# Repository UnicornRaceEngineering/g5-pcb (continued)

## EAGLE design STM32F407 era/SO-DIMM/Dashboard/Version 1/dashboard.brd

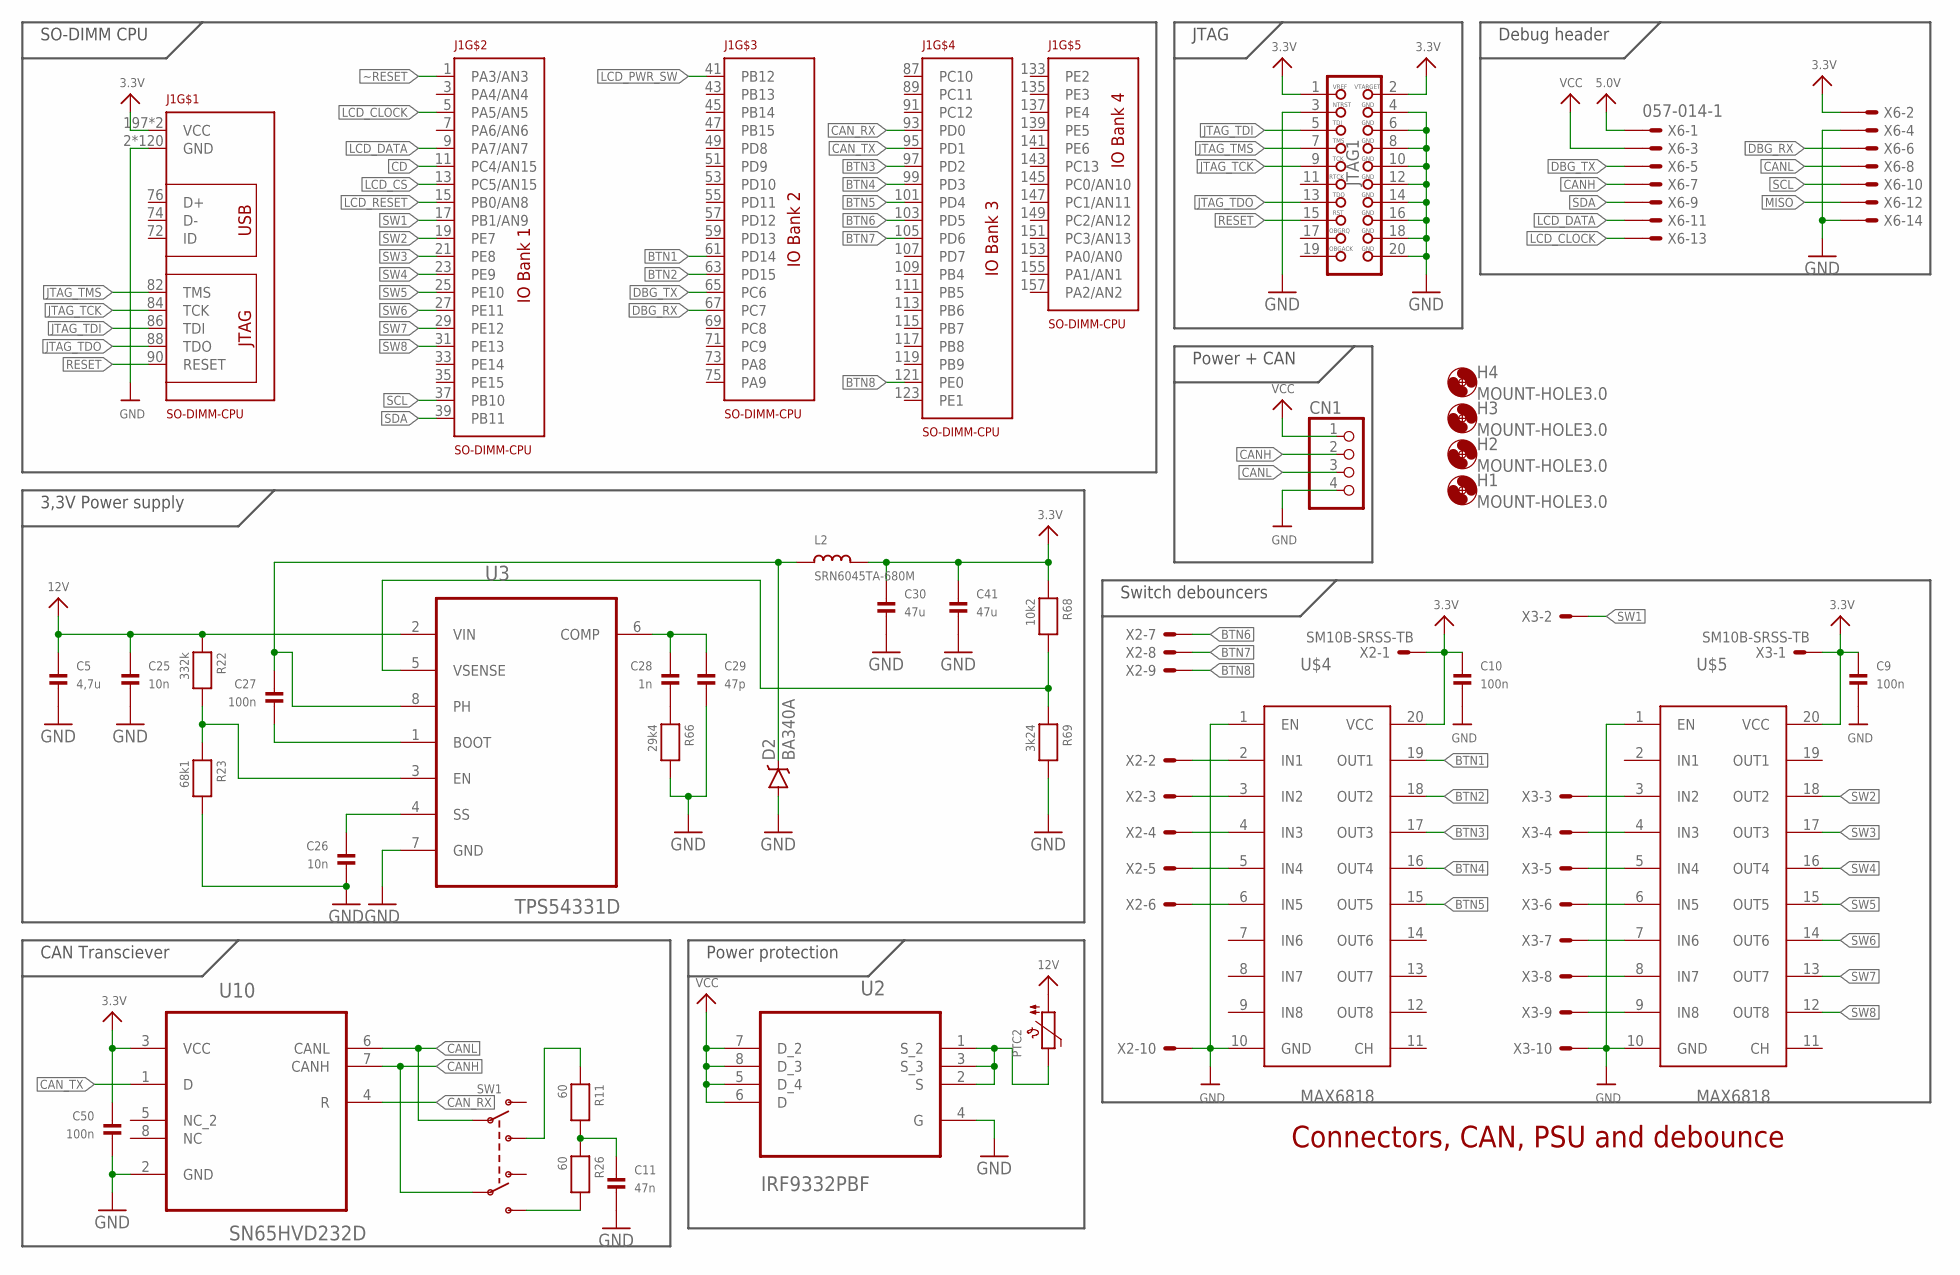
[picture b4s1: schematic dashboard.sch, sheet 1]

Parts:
C5: 4,7u; _0805
C9, C10, C27, C50: 100n; _0603
C11: 47n; _0603
C25, C26: 10n; _0603
C28: 1n; _0603
C29: 47p; _0603
C30, C41: 47u; _0805
CN1: JST_4PIN; JSTPH4
D2: BA340A; SMA-DIODE
H1, H2, H3, H4: MOUNT-HOLE3.0; 3,0
J1: SO-DIMM-CPU; SODIMM-CONNECTOR-2.5V
JTAG1: JTAG-ARM
L2: SRN6045TA-680M; INDUCTOR_6X6MM_TDK_VLC6045
PTC2: PTC1812
R11, R26: 60; _0603
R22: 332k; _0603
R23: 68k1; _0603
R66: 29k4; _0603
R68: 10k2; _0603
R69: 3k24; _0603
SW1: SWITCH_DPDT; DPDT_SMT_JS202011SCQN
U2: IRF9332PBF; SOIC127P600X175-8N
U3: TPS54331D; SOIC127P600X175-8N
U10: SN65HVD232D; SOIC127P600X175-8N
U$4, U$5: MAX6818; SOP20
X2, X3: SM10B-SRSS-TB
X6: 057-014-1

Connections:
3.3V: C9.1, C10.1, C30.1, C41.1, C50.1, J1.197 (VCC), J1.199 (VCC), JTAG1.1, JTAG1.2, L2.P$2 (2), R68.1, U10.3 (VCC), U$4.20 (VCC), U$5.20 (VCC), X2.1, X3.1, X6.2; also elsewhere on the board
5.0V: X6.1
12V: C5.1, C25.1, PTC2.P$1 (1), R22.1, U3.2 (VIN)
BTN1: J1.61 (PD14), U$4.19 (OUT1)
BTN2: J1.63 (PD15), U$4.18 (OUT2)
BTN3: J1.97 (PD2), U$4.17 (OUT3)
BTN4: J1.99 (PD3), U$4.16 (OUT4)
BTN5: J1.101 (PD4), U$4.15 (OUT5)
BTN6: J1.103 (PD5), X2.7
BTN7: J1.105 (PD6), X2.8
BTN8: J1.121 (PE0), X2.9
CANH: CN1.2, SW1.P$5 (P2), U10.7 (CANH), X6.7
CANL: CN1.3, SW1.P$2 (P1), U10.6 (CANL), X6.8
CAN_RX: J1.93 (PD0), U10.4 (R)
CAN_TX: J1.95 (PD1), U10.1 (D)
CD: J1.11 (PC4/AN15); also elsewhere on the board
DBG_RX: J1.67 (PC7), X6.6
DBG_TX: J1.65 (PC6), X6.5
GND: C5.2, C9.2, C10.2, C11.2, C25.2, C26.2, C29.2, C30.2, C41.2, C50.2, CN1.4, D2.A, J1.2 (GND), J1.4 (GND), J1.6 (GND), J1.8 (GND), J1.10 (GND), J1.12 (GND), J1.14 (GND), J1.16 (GND), J1.18 (GND), J1.20 (GND), J1.22 (GND), J1.24 (GND), J1.26 (GND), J1.28 (GND), J1.30 (GND), J1.32 (GND), J1.34 (GND), J1.36 (GND), J1.38 (GND), J1.40 (GND), J1.42 (GND), J1.44 (GND), J1.46 (GND), J1.48 (GND), J1.50 (GND), J1.52 (GND), J1.54 (GND), J1.56 (GND), J1.58 (GND), J1.60 (GND), J1.62 (GND), J1.64 (GND), J1.66 (GND), J1.68 (GND), J1.70 (GND), J1.77 (GND), J1.78 (GND), J1.79 (GND), J1.80 (GND), J1.81 (GND), J1.83 (GND), J1.85 (GND), J1.92 (GND), J1.94 (GND), J1.96 (GND), J1.98 (GND), J1.100 (GND), J1.102 (GND), J1.104 (GND), J1.106 (GND), J1.108 (GND), J1.110 (GND), J1.112 (GND), J1.114 (GND), J1.116 (GND), J1.118 (GND), J1.120 (GND), J1.122 (GND), J1.124 (GND), J1.125 (GND), J1.126 (GND), J1.127 (GND), J1.128 (GND), J1.129 (GND), J1.130 (GND), J1.131 (GND), J1.132 (GND), J1.134 (GND), J1.136 (GND), J1.138 (GND), J1.140 (GND), J1.142 (GND), J1.144 (GND), J1.146 (GND), J1.148 (GND), J1.150 (GND), J1.152 (GND), J1.154 (GND), J1.156 (GND), J1.158 (GND), J1.159 (GND), J1.160 (GND), J1.161 (GND), J1.162 (GND), J1.163 (GND), J1.164 (GND), J1.165 (GND), J1.166 (GND), J1.167 (GND), J1.168 (GND), J1.169 (GND), J1.170 (GND), J1.171 (GND), J1.172 (GND), J1.173 (GND), J1.174 (GND), J1.175 (GND), J1.176 (GND), J1.177 (GND), J1.178 (GND), J1.179 (GND), J1.180 (GND), J1.181 (GND), J1.182 (GND), J1.183 (GND), J1.184 (GND), J1.185 (GND), J1.186 (GND), J1.187 (GND), J1.188 (GND), J1.189 (GND), J1.190 (GND), J1.191 (GND), J1.192 (GND), J1.193 (GND), J1.194 (GND), J1.195 (GND), J1.196 (GND), J1.198 (GND), J1.200 (GND), JTAG1.3, JTAG1.4, JTAG1.6, JTAG1.8, JTAG1.10, JTAG1.12, JTAG1.14, JTAG1.16, JTAG1.18, JTAG1.20, R23.2, R66.2, R69.2, U2.4 (G), U3.7 (GND), U10.2 (GND), U$4.1 (EN), U$4.10 (GND), U$5.1 (EN), U$5.10 (GND), X2.10, X3.10, X6.4, X6.14; also elsewhere on the board
JTAG_TCK: J1.84 (TCK), JTAG1.9
JTAG_TDI: J1.86 (TDI), JTAG1.5
JTAG_TDO: J1.88 (TDO), JTAG1.13
JTAG_TMS: J1.82 (TMS), JTAG1.7
LCD_CLOCK: J1.5 (PA5/AN5), X6.13; also elsewhere on the board
LCD_CS: J1.13 (PC5/AN15); also elsewhere on the board
LCD_DATA: J1.9 (PA7/AN7), X6.11; also elsewhere on the board
LCD_PWR_SW: J1.41 (PB12); also elsewhere on the board
LCD_RESET: J1.15 (PB0/AN8); also elsewhere on the board
MISO: X6.12
unnamed: C26.1, U3.4 (SS)
unnamed: R22.2, R23.1, U3.3 (EN)
unnamed: C27.2, U3.1 (BOOT)
unnamed: C27.1, D2.C, L2.P$1 (1), U3.8 (PH)
unnamed: C28.2, R66.1
unnamed: C28.1, C29.1, U3.6 (COMP)
unnamed: R68.2, R69.1, U3.5 (VSENSE)
unnamed: PTC2.P$2 (2), U2.1 (S_2), U2.2 (S), U2.3 (S_3)
unnamed: R26.2, SW1.P$4 (S2)
unnamed: C11.1, R11.2, R26.1
unnamed: U$4.2 (IN1), X2.2
unnamed: U$5.3 (IN2), X3.3
unnamed: U$5.4 (IN3), X3.4
unnamed: U$5.5 (IN4), X3.5
unnamed: U$5.6 (IN5), X3.6
unnamed: U$5.7 (IN6), X3.7
unnamed: U$5.8 (IN7), X3.8
unnamed: U$5.9 (IN8), X3.9
unnamed: U$4.3 (IN2), X2.3
unnamed: U$4.4 (IN3), X2.4
unnamed: U$4.5 (IN4), X2.5
unnamed: U$4.6 (IN5), X2.6
unnamed: R11.1, SW1.P$3 (S1)
RESET: J1.90 (RESET), JTAG1.15
SCL: J1.37 (PB10), X6.10; also elsewhere on the board
SDA: J1.39 (PB11), X6.9; also elsewhere on the board
SW1: J1.17 (PB1/AN9), X3.2
SW2: J1.19 (PE7), U$5.18 (OUT2)
SW3: J1.21 (PE8), U$5.17 (OUT3)
SW4: J1.23 (PE9), U$5.16 (OUT4)
SW5: J1.25 (PE10), U$5.15 (OUT5)
SW6: J1.27 (PE11), U$5.14 (OUT6)
SW7: J1.29 (PE12), U$5.13 (OUT7)
SW8: J1.31 (PE13), U$5.12 (OUT8)
VCC: CN1.1, U2.5 (D_4), U2.6 (D), U2.7 (D_2), U2.8 (D_3), X6.3
~RESET: J1.1 (PA3/AN3); also elsewhere on the board

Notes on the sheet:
3,3V Power supply
Power protection
CAN Transciever
JTAG
Debug header
SO-DIMM CPU
Power + CAN
Switch debouncers
Connectors, CAN, PSU and debounce

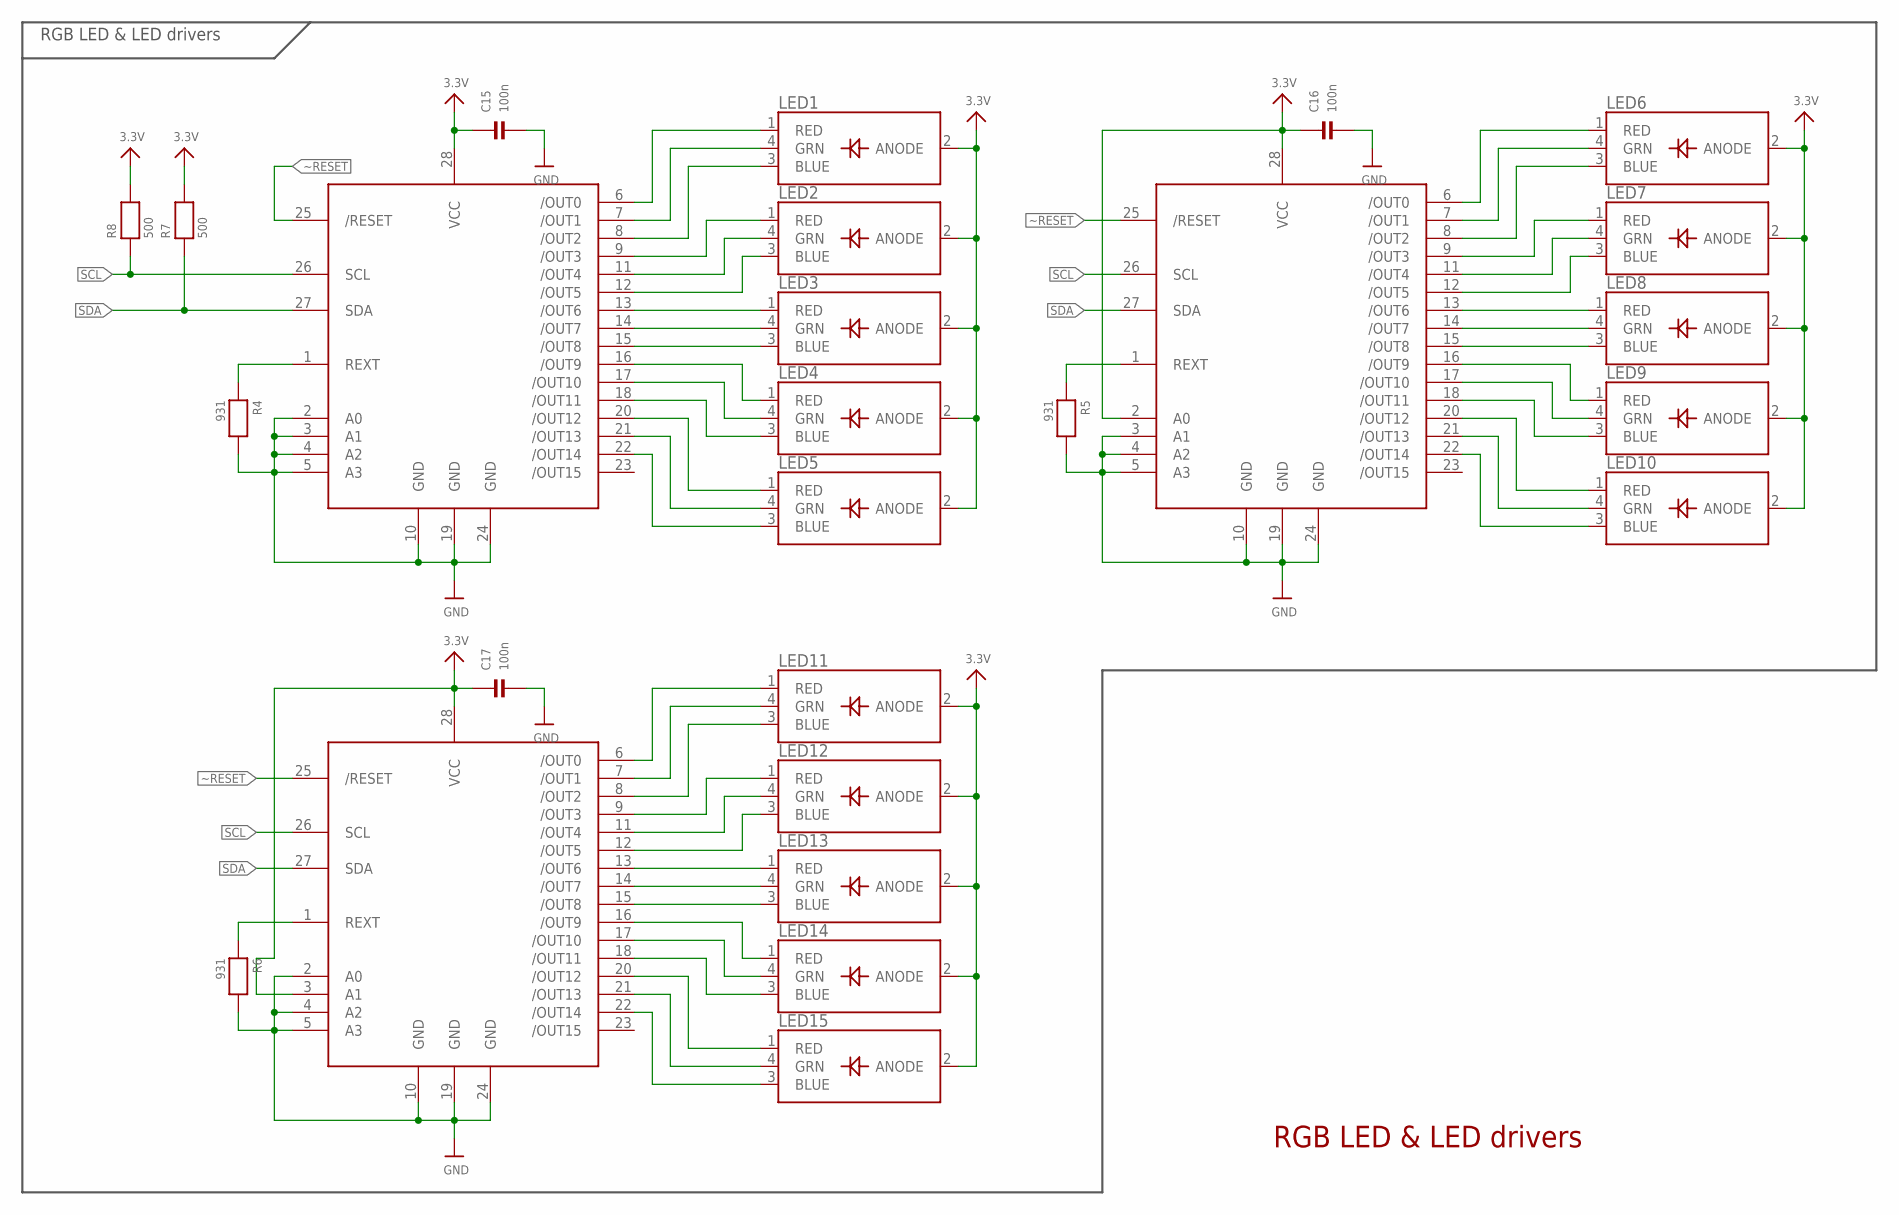
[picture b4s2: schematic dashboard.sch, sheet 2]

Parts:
C15, C16, C17: 100n; _0603
LED1, LED2, LED3, LED4, LED5, LED6, LED7, LED8, LED9, LED10, LED11, LED12, LED13, LED14, LED15: LED_RGB_PLCC4; RGBLED_PLCC4
R4, R5, R6: 931; _0603
R7, R8: 500; _0603
U$30, U$33, U$36: TLC59116; TSSOP28

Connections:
3.3V: C15.1, C16.1, C17.1, LED1.2 (ANODE), LED2.2 (ANODE), LED3.2 (ANODE), LED4.2 (ANODE), LED5.2 (ANODE), LED6.2 (ANODE), LED7.2 (ANODE), LED8.2 (ANODE), LED9.2 (ANODE), LED10.2 (ANODE), LED11.2 (ANODE), LED12.2 (ANODE), LED13.2 (ANODE), LED14.2 (ANODE), LED15.2 (ANODE), R7.2, R8.2, U$30.28 (VCC), U$33.2 (A0), U$33.28 (VCC), U$36.3 (A1), U$36.28 (VCC); also elsewhere on the board
GND: C15.2, C16.2, C17.2, R4.2, R5.2, R6.2, U$30.2 (A0), U$30.3 (A1), U$30.4 (A2), U$30.5 (A3), U$30.10 (GND), U$30.19 (GND), U$30.24 (GND), U$33.3 (A1), U$33.4 (A2), U$33.5 (A3), U$33.10 (GND), U$33.19 (GND), U$33.24 (GND), U$36.2 (A0), U$36.4 (A2), U$36.5 (A3), U$36.10 (GND), U$36.19 (GND), U$36.24 (GND); also elsewhere on the board
unnamed: LED1.1 (RED), U$30.6 (/OUT0)
unnamed: LED1.4 (GRN), U$30.7 (/OUT1)
unnamed: LED1.3 (BLUE), U$30.8 (/OUT2)
unnamed: LED2.1 (RED), U$30.9 (/OUT3)
unnamed: LED2.4 (GRN), U$30.11 (/OUT4)
unnamed: LED2.3 (BLUE), U$30.12 (/OUT5)
unnamed: LED3.1 (RED), U$30.13 (/OUT6)
unnamed: LED3.4 (GRN), U$30.14 (/OUT7)
unnamed: LED3.3 (BLUE), U$30.15 (/OUT8)
unnamed: LED4.1 (RED), U$30.16 (/OUT9)
unnamed: LED4.4 (GRN), U$30.17 (/OUT10)
unnamed: LED4.3 (BLUE), U$30.18 (/OUT11)
unnamed: LED5.1 (RED), U$30.20 (/OUT12)
unnamed: LED5.4 (GRN), U$30.21 (/OUT13)
unnamed: LED5.3 (BLUE), U$30.22 (/OUT14)
unnamed: LED6.1 (RED), U$33.6 (/OUT0)
unnamed: LED6.4 (GRN), U$33.7 (/OUT1)
unnamed: LED6.3 (BLUE), U$33.8 (/OUT2)
unnamed: LED7.1 (RED), U$33.9 (/OUT3)
unnamed: LED7.4 (GRN), U$33.11 (/OUT4)
unnamed: LED7.3 (BLUE), U$33.12 (/OUT5)
unnamed: LED8.1 (RED), U$33.13 (/OUT6)
unnamed: LED8.4 (GRN), U$33.14 (/OUT7)
unnamed: LED8.3 (BLUE), U$33.15 (/OUT8)
unnamed: LED9.1 (RED), U$33.16 (/OUT9)
unnamed: LED9.4 (GRN), U$33.17 (/OUT10)
unnamed: LED9.3 (BLUE), U$33.18 (/OUT11)
unnamed: LED10.1 (RED), U$33.20 (/OUT12)
unnamed: LED10.4 (GRN), U$33.21 (/OUT13)
unnamed: LED10.3 (BLUE), U$33.22 (/OUT14)
unnamed: LED11.1 (RED), U$36.6 (/OUT0)
unnamed: LED11.4 (GRN), U$36.7 (/OUT1)
unnamed: LED11.3 (BLUE), U$36.8 (/OUT2)
unnamed: LED12.1 (RED), U$36.9 (/OUT3)
unnamed: LED12.4 (GRN), U$36.11 (/OUT4)
unnamed: LED12.3 (BLUE), U$36.12 (/OUT5)
unnamed: LED13.1 (RED), U$36.13 (/OUT6)
unnamed: LED13.4 (GRN), U$36.14 (/OUT7)
unnamed: LED13.3 (BLUE), U$36.15 (/OUT8)
unnamed: LED14.1 (RED), U$36.16 (/OUT9)
unnamed: LED14.4 (GRN), U$36.17 (/OUT10)
unnamed: LED14.3 (BLUE), U$36.18 (/OUT11)
unnamed: LED15.1 (RED), U$36.20 (/OUT12)
unnamed: LED15.4 (GRN), U$36.21 (/OUT13)
unnamed: LED15.3 (BLUE), U$36.22 (/OUT14)
unnamed: R4.1, U$30.1 (REXT)
unnamed: R5.1, U$33.1 (REXT)
unnamed: R6.1, U$36.1 (REXT)
SCL: R8.1, U$30.26 (SCL), U$33.26 (SCL), U$36.26 (SCL); also elsewhere on the board
SDA: R7.1, U$30.27 (SDA), U$33.27 (SDA), U$36.27 (SDA); also elsewhere on the board
~RESET: U$30.25 (/RESET), U$33.25 (/RESET), U$36.25 (/RESET); also elsewhere on the board

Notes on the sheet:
RGB LED & LED drivers

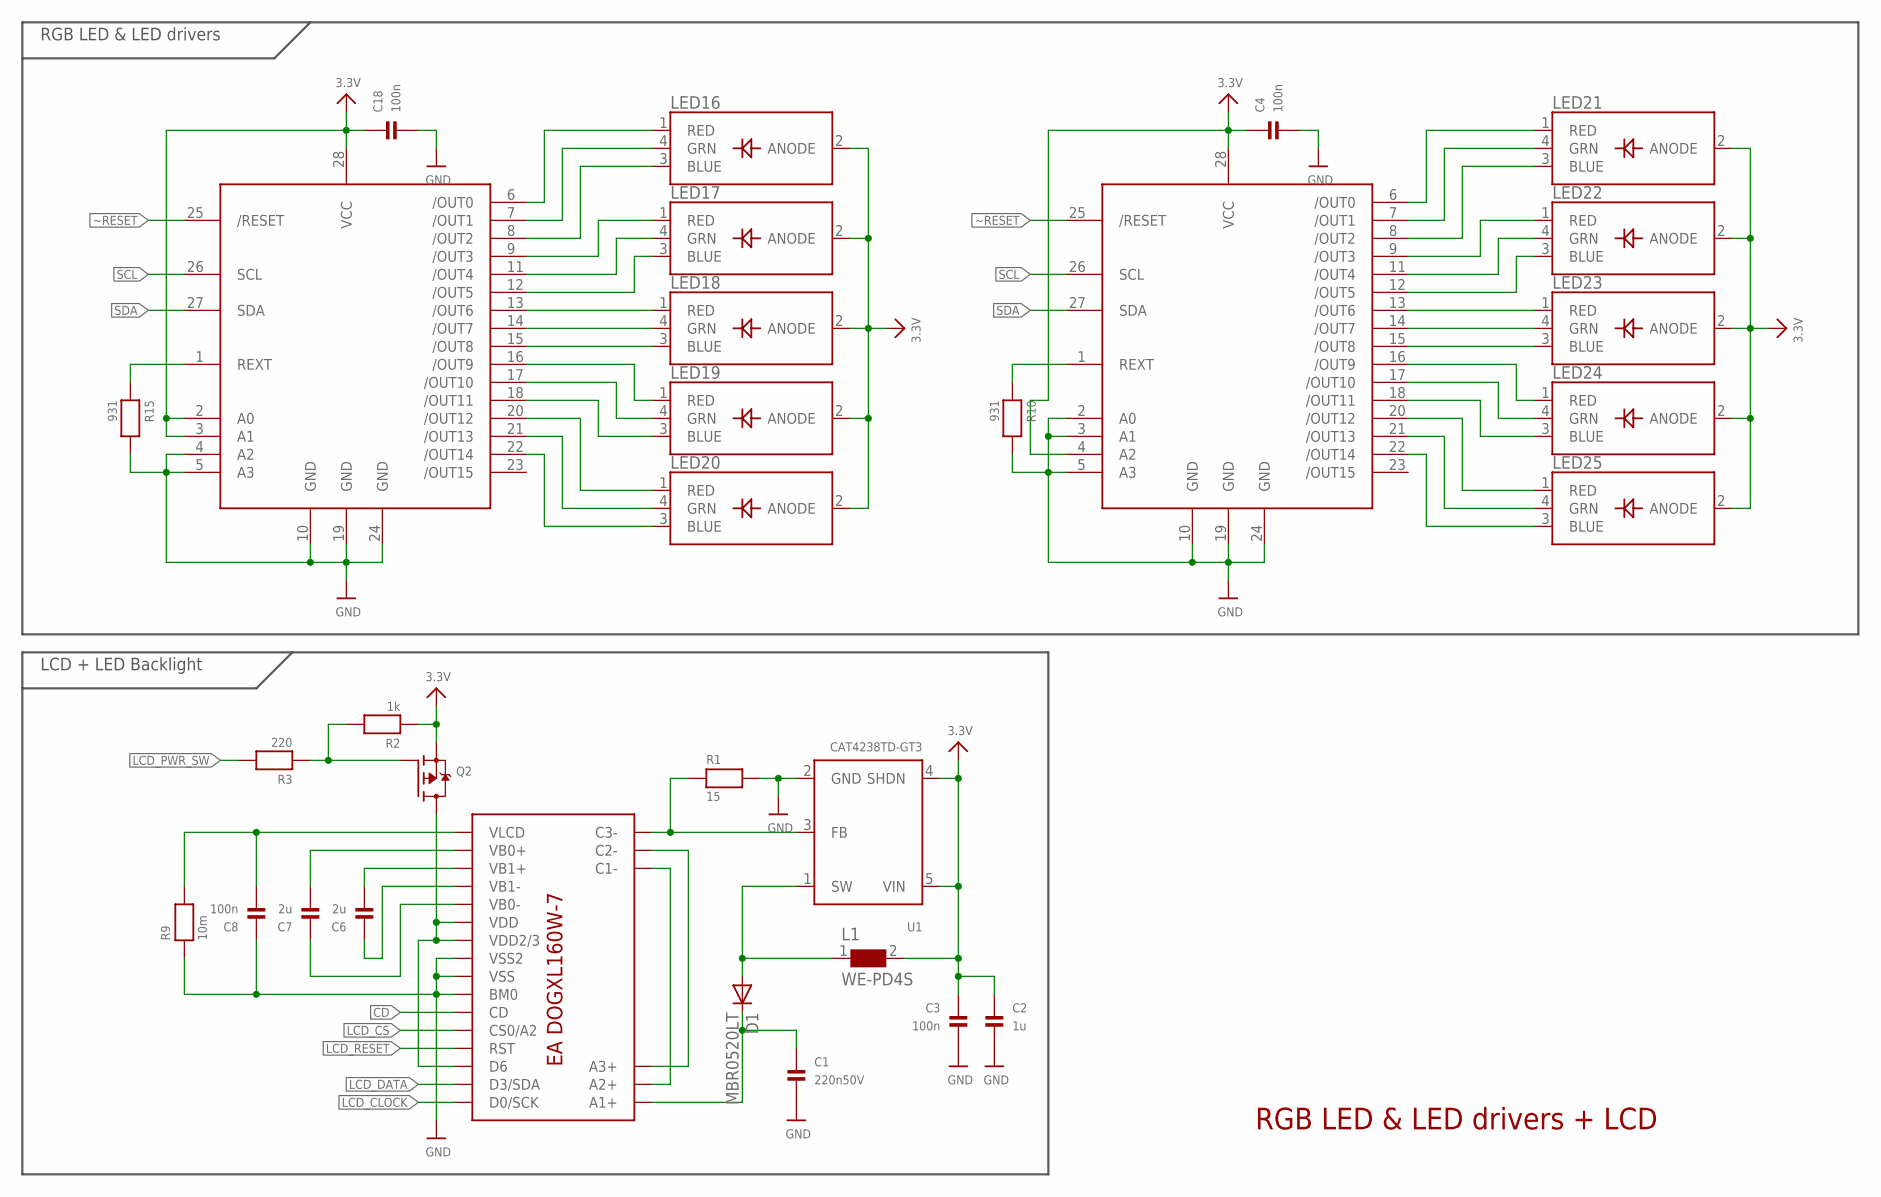
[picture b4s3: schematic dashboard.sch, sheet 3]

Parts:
C1: 220n50V; _0805
C2: 1u; _0805
C3, C4, C8, C18: 100n; _0603
C6, C7: 2u; _0805
D1: MBR0520LT; SOD123
L1: WE-PD4S; S
LED16, LED17, LED18, LED19, LED20, LED21, LED22, LED23, LED24, LED25: LED_RGB_PLCC4; RGBLED_PLCC4
Q2: MOSFET-PWIDE; SOT23-WIDE
R1: 15; _0603
R2: 1k; _0603
R3: 220; _0603
R9: 10m; _0805
R10, R15: 931; _0603
U1: CAT4238TD-GT3; SOT23-5
U$8, U$51: TLC59116; TSSOP28
U$10: EA-DOGXL160W-7

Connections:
3.3V: C2.1, C3.1, C4.1, C18.1, L1.2, LED16.2 (ANODE), LED17.2 (ANODE), LED18.2 (ANODE), LED19.2 (ANODE), LED20.2 (ANODE), LED21.2 (ANODE), LED22.2 (ANODE), LED23.2 (ANODE), LED24.2 (ANODE), LED25.2 (ANODE), Q2.2 (S), R2.1, U1.4 (SHDN), U1.5 (VIN), U$8.4 (A2), U$8.28 (VCC), U$51.2 (A0), U$51.3 (A1), U$51.28 (VCC); also elsewhere on the board
CD: U$10.P$27 (CD); also elsewhere on the board
GND: C1.2, C2.2, C3.2, C4.2, C8.1, C18.2, R1.2, R9.1, R10.2, R15.2, U1.2 (GND), U$8.2 (A0), U$8.3 (A1), U$8.5 (A3), U$8.10 (GND), U$8.19 (GND), U$8.24 (GND), U$10.P$24 (VSS2), U$10.P$25 (VSS), U$10.P$26 (BM0), U$51.4 (A2), U$51.5 (A3), U$51.10 (GND), U$51.19 (GND), U$51.24 (GND); also elsewhere on the board
LCD_CLOCK: U$10.P$32 (D0/SCK); also elsewhere on the board
LCD_CS: U$10.P$28 (CS0/A2); also elsewhere on the board
LCD_DATA: U$10.P$31 (D3/SDA); also elsewhere on the board
LCD_PWR_SW: R3.2; also elsewhere on the board
LCD_RESET: U$10.P$29 (RST); also elsewhere on the board
unnamed: U$10.P$2 (A2+), U$10.P$14 (C1-)
unnamed: U$10.P$3 (A3+), U$10.P$15 (C2-)
unnamed: R1.1, U1.3 (FB), U$10.P$16 (C3-)
unnamed: C1.1, D1.C, U$10.P$1 (A1+)
unnamed: D1.A, L1.1, U1.1 (SW)
unnamed: Q2.3 (D), U$10.P$22 (VDD), U$10.P$23 (VDD2/3), U$10.P$30 (D6)
unnamed: Q2.1 (G), R2.2, R3.1
unnamed: LED16.1 (RED), U$51.6 (/OUT0)
unnamed: C6.1, U$10.P$20 (VB1-)
unnamed: C7.1, U$10.P$21 (VB0-)
unnamed: C6.2, U$10.P$19 (VB1+)
unnamed: C7.2, U$10.P$18 (VB0+)
unnamed: C8.2, R9.2, U$10.P$17 (VLCD)
unnamed: LED16.4 (GRN), U$51.7 (/OUT1)
unnamed: LED16.3 (BLUE), U$51.8 (/OUT2)
unnamed: LED17.1 (RED), U$51.9 (/OUT3)
unnamed: LED17.4 (GRN), U$51.11 (/OUT4)
unnamed: LED17.3 (BLUE), U$51.12 (/OUT5)
unnamed: LED18.1 (RED), U$51.13 (/OUT6)
unnamed: LED18.4 (GRN), U$51.14 (/OUT7)
unnamed: LED18.3 (BLUE), U$51.15 (/OUT8)
unnamed: LED19.1 (RED), U$51.16 (/OUT9)
unnamed: LED19.4 (GRN), U$51.17 (/OUT10)
unnamed: LED19.3 (BLUE), U$51.18 (/OUT11)
unnamed: LED20.1 (RED), U$51.20 (/OUT12)
unnamed: LED20.4 (GRN), U$51.21 (/OUT13)
unnamed: LED20.3 (BLUE), U$51.22 (/OUT14)
unnamed: R15.1, U$51.1 (REXT)
unnamed: LED21.1 (RED), U$8.6 (/OUT0)
unnamed: LED21.4 (GRN), U$8.7 (/OUT1)
unnamed: LED21.3 (BLUE), U$8.8 (/OUT2)
unnamed: LED22.1 (RED), U$8.9 (/OUT3)
unnamed: LED22.4 (GRN), U$8.11 (/OUT4)
unnamed: LED22.3 (BLUE), U$8.12 (/OUT5)
unnamed: LED23.1 (RED), U$8.13 (/OUT6)
unnamed: LED23.4 (GRN), U$8.14 (/OUT7)
unnamed: LED23.3 (BLUE), U$8.15 (/OUT8)
unnamed: LED24.1 (RED), U$8.16 (/OUT9)
unnamed: LED24.4 (GRN), U$8.17 (/OUT10)
unnamed: LED24.3 (BLUE), U$8.18 (/OUT11)
unnamed: LED25.1 (RED), U$8.20 (/OUT12)
unnamed: LED25.4 (GRN), U$8.21 (/OUT13)
unnamed: LED25.3 (BLUE), U$8.22 (/OUT14)
unnamed: R10.1, U$8.1 (REXT)
SCL: U$8.26 (SCL), U$51.26 (SCL); also elsewhere on the board
SDA: U$8.27 (SDA), U$51.27 (SDA); also elsewhere on the board
~RESET: U$8.25 (/RESET), U$51.25 (/RESET); also elsewhere on the board

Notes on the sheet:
RGB LED & LED drivers + LCD
RGB LED & LED drivers
LCD + LED Backlight

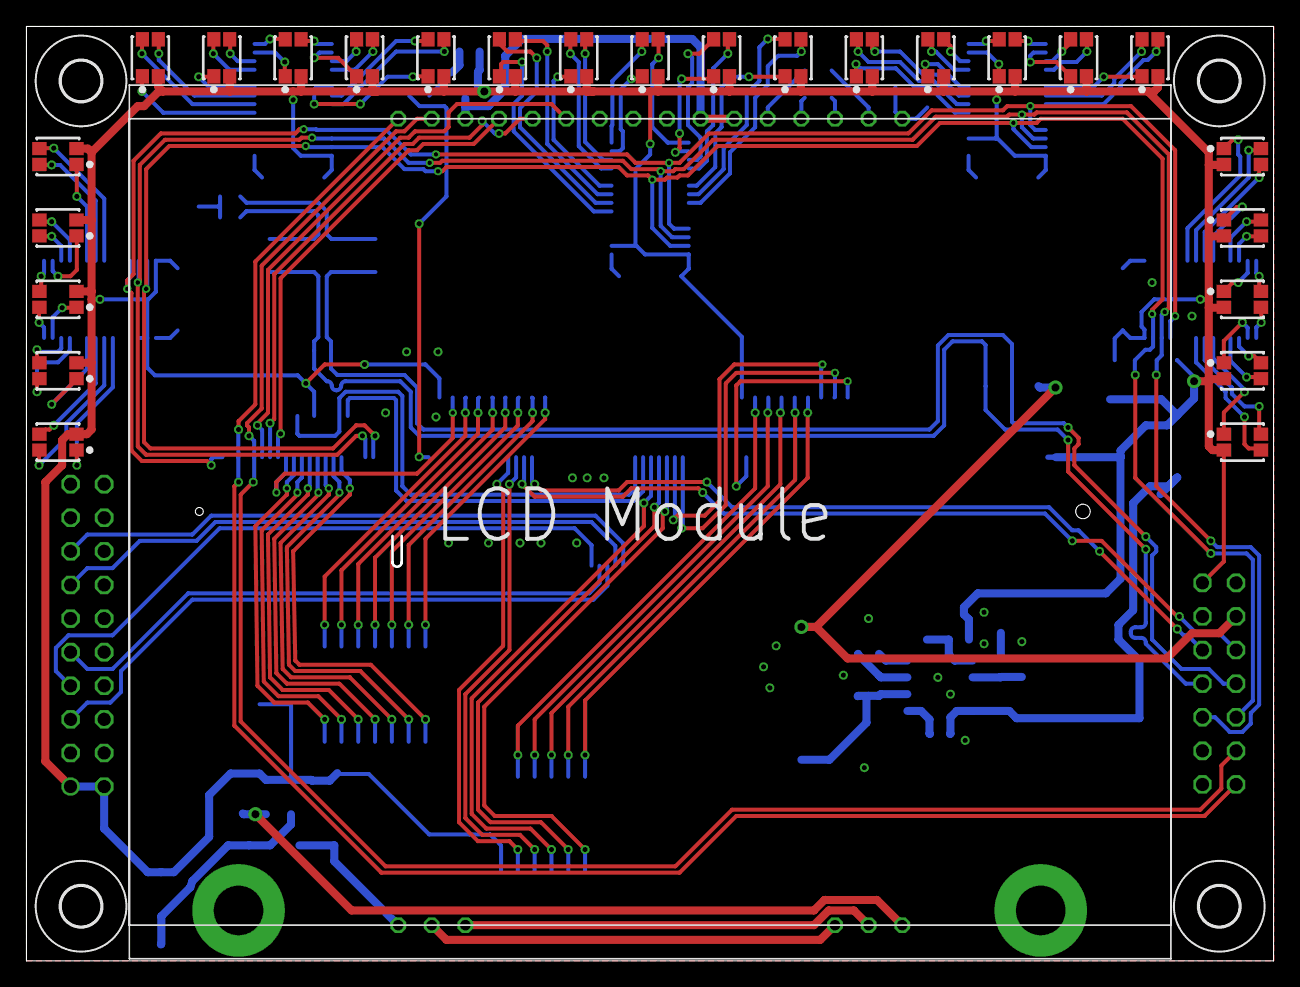
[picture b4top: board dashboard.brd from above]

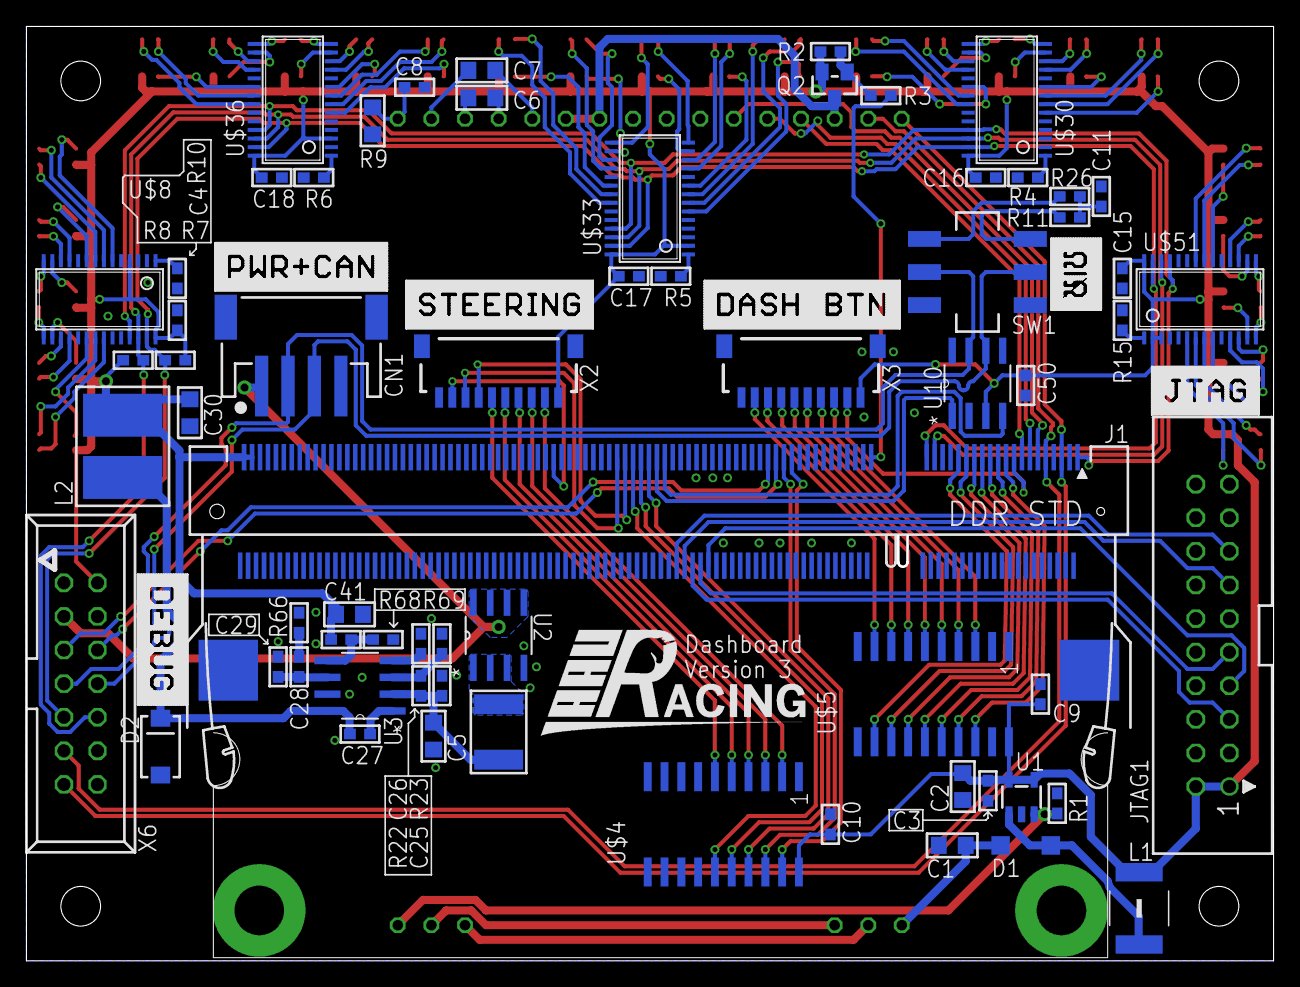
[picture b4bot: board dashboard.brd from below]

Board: 2 copper layers, 94.3 x 70.6 mm, 95 parts (65 on the bottom side), 155 nets.

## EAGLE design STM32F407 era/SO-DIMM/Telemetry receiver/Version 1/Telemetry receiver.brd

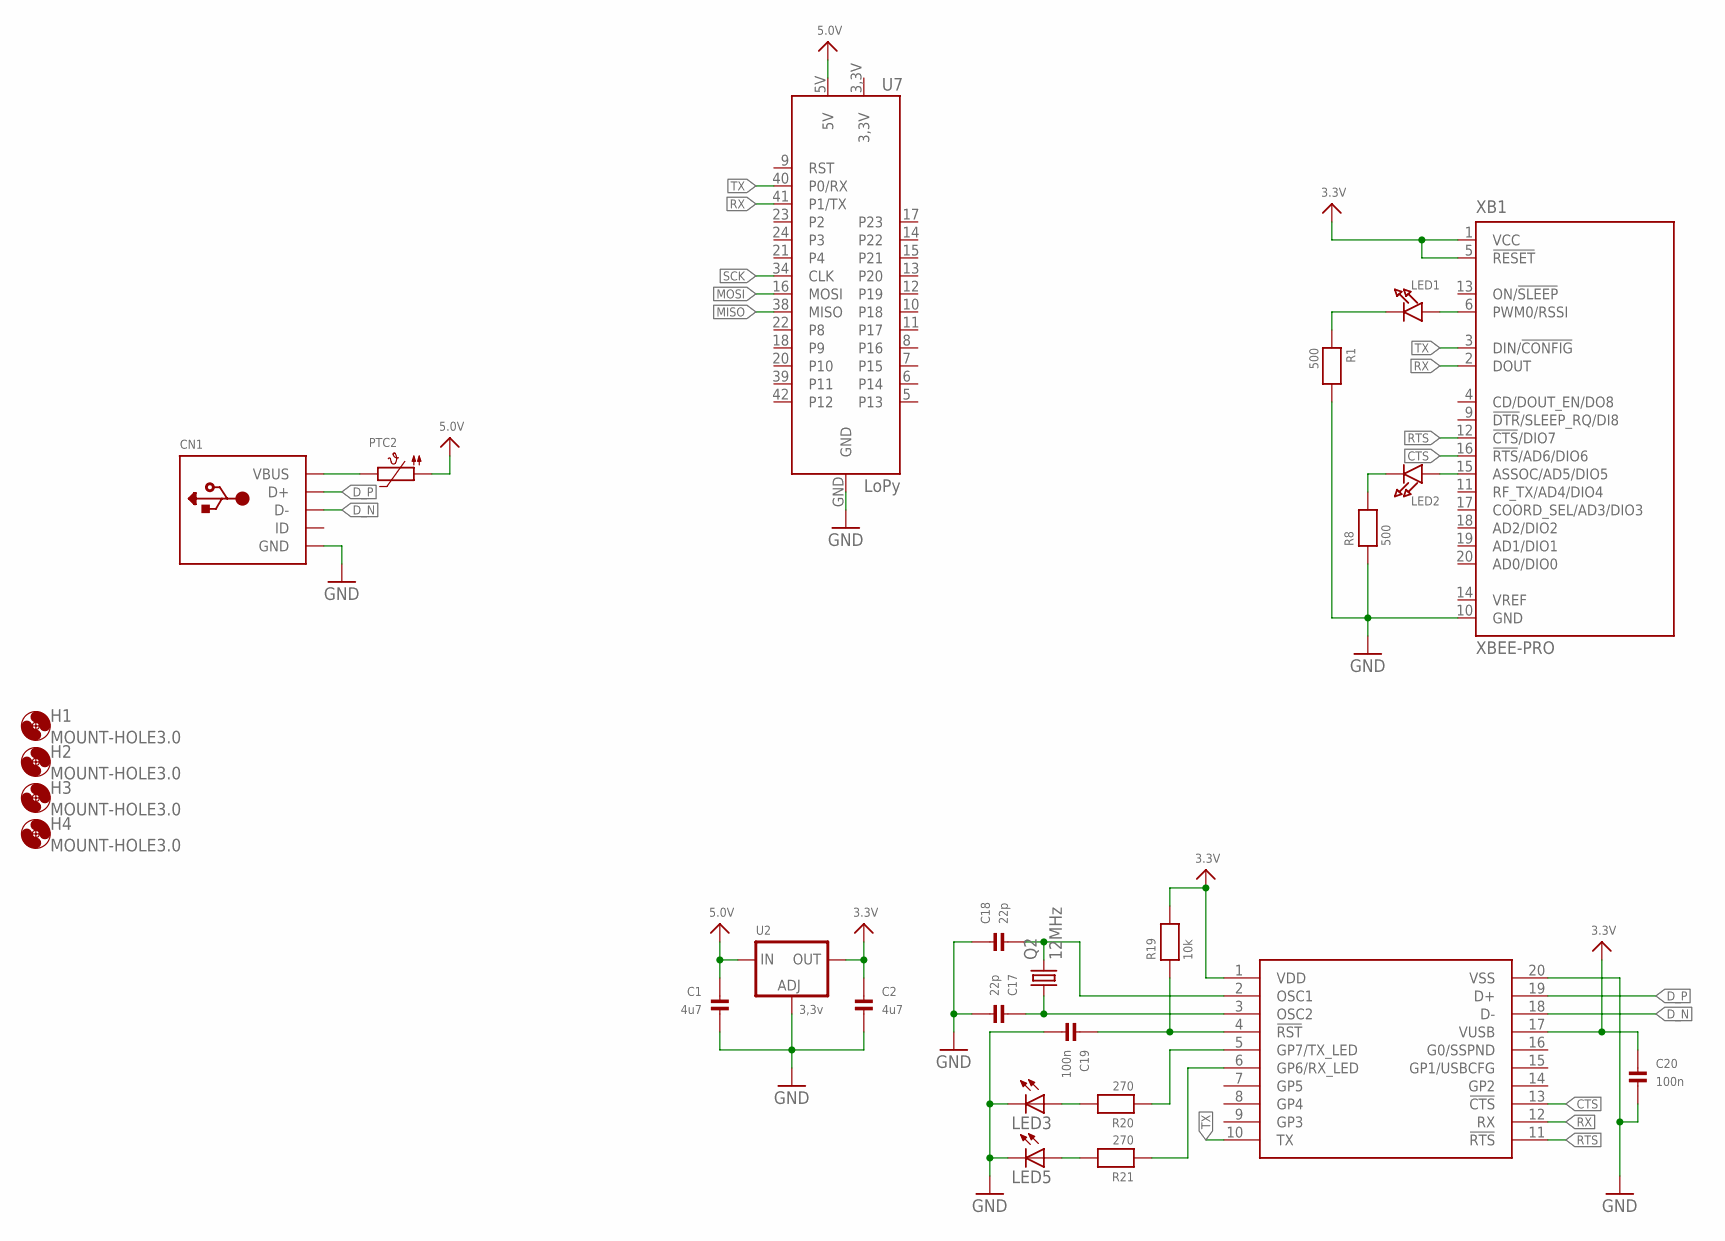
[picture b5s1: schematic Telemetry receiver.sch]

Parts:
C1, C2: 4u7; _0805
C17, C18: 22p; _0603
C19, C20: 100n; _0603
CN1: USBMINIBLARGE; USB-MINIB_LARGER
H1, H2, H3, H4: MOUNT-HOLE3.0; 3,0
LED1, LED2: LED1206; CHIPLED_1206
LED3, LED5: LEDCHIPLED_0805; CHIPLED_0805
PTC2: PTC1812
Q2: 12MHz; HC49/S
R1, R8: 500; _0603
R19: 10k; _0603
R20, R21: 270; _0603
U2: 3,3v; SOT223-R
U7: LoPy; LOPY
U$24: MCP2200; SO20L
XB1: XBEE-PRO

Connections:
3.3V: C2.1, C20.1, R19.2, U2.2 (OUT), U$24.1 (VDD), U$24.17 (VUSB), XB1.1 (VCC), XB1.5 (!RESET)
5.0V: C1.1, PTC2.P$1 (1), U2.3 (IN), U7.5V
CTS: U$24.13 (!CTS), XB1.16 (!RTS!/AD6/DIO6)
D_N: CN1.D-, U$24.18 (D-)
D_P: CN1.D+, U$24.19 (D+)
GND: C1.2, C2.2, C17.2, C18.1, C19.2, C20.2, CN1.GND, LED3.C, LED5.C, R1.2, R8.1, U2.1 (ADJ), U7.GND, U$24.20 (VSS), XB1.10 (GND)
MISO: U7.38 (MISO)
MOSI: U7.16 (MOSI)
unnamed: CN1.VBUS, PTC2.P$2 (2)
unnamed: LED1.A, XB1.6 (PWM0/RSSI)
unnamed: LED1.C, R1.1
unnamed: LED2.A, XB1.15 (ASSOC/AD5/DIO5)
unnamed: LED2.C, R8.2
unnamed: C18.2, Q2.2, U$24.2 (OSC1)
unnamed: C17.1, Q2.1, U$24.3 (OSC2)
unnamed: R21.1, U$24.6 (GP6/RX_LED)
unnamed: R20.1, U$24.5 (GP7/TX_LED)
unnamed: C19.1, R19.1, U$24.4 (!RST)
unnamed: LED3.A, R20.2
unnamed: LED5.A, R21.2
RTS: U$24.11 (!RTS), XB1.12 (!CTS!/DIO7)
RX: U7.41 (P1/TX), U$24.12 (RX), XB1.2 (DOUT)
SCK: U7.34 (CLK)
TX: U7.40 (P0/RX), U$24.10 (TX), XB1.3 (DIN/!CONFIG)

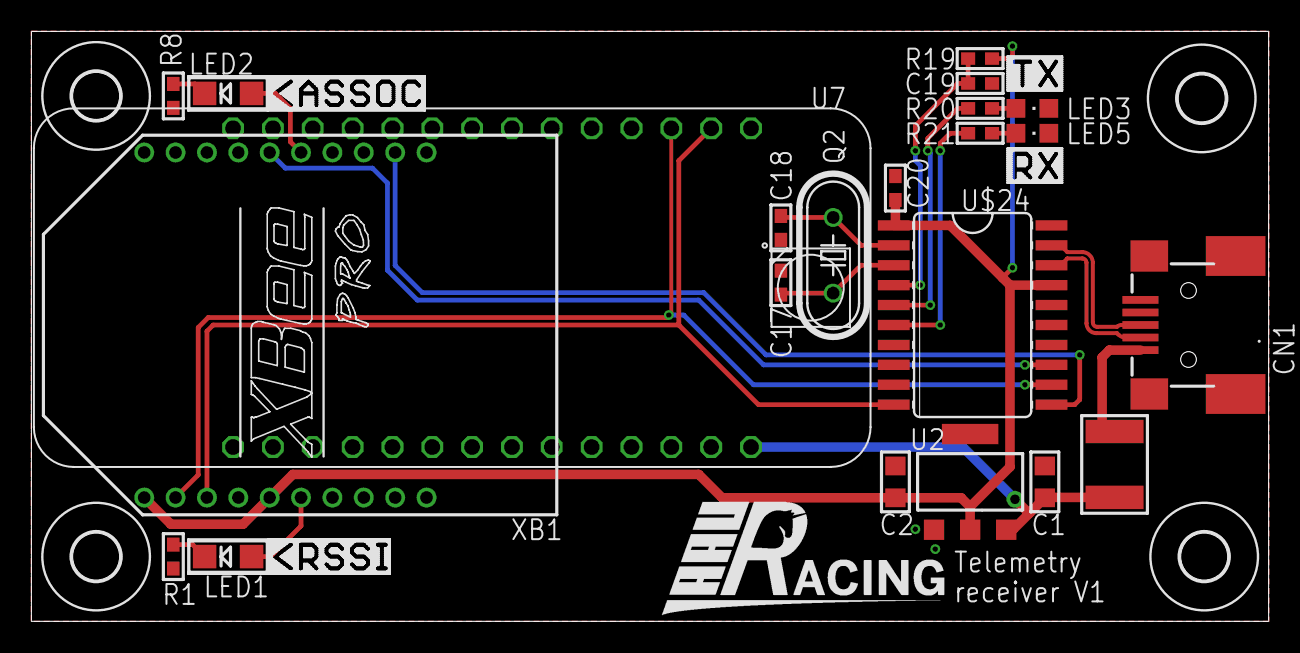
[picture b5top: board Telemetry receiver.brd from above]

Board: 2 copper layers, 78.9 x 37.6 mm, 26 parts (0 on the bottom side), 21 nets.
